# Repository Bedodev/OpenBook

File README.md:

# OpenBook
OpenBook is an open Source eBook Project that aims to create a simple yet powerful esp32-based ebook reader, with quality of life features. 

## Block Diagram

## Simplified BoM
Component | Part # | Source Link
--- | --- | ---
ESP32 | ESP32-C6-WROOM-1-N8 | [Mouser](https://mou.sr/42swLfH)
MicroSD Card Reader | 112A-TAAR-R03 | [DigiKey](https://www.digikey.ro/en/models/17633923)
NOR Flash | W25Q512JVEIQ | [ComponentSearchengine](https://componentsearchengine.com/search?term=W25Q512JVEIQ)
Adafruit Led | SM0603UYC | [SnapEda](https://www.snapeda.com/parts/SM0603UYC/Bivar/view-part/)
Environment Sensor | BME680 | [DigiKey](https://www.digikey.lt/en/models/7401317)
Super Capacitor | CPH3225A-2K | [SnapMagic](https://www.snapeda.com/parts/CPH3225A-2K/Seiko/view-part/)
0402 capsule | RC0402 | [GrabCad](https://grabcad.com/library/tag/0402)
Tantalum Capacitor | TR3B106K025C1300 | [Mouser](https://eu.mouser.com/ProductDetail/Vishay-Sprague/TR3B106K025C1300?qs=jCGqFXxTmLdffnuDkXzk1g%3D%3D)
RTC | DS3231SN# | [ComponentSearchEngine](https://componentsearchengine.com/part-view/DS3231SN%23/Analog%20Devices)
Voltage Detector | BD5229G-TR | [ComponentSearchEngine](https://componentsearchengine.com/part-view/BD5229G-TR/ROHM%20Semiconductor)
Right Angle Switches | EVQ-P7M01P | [Mouser](https://mou.sr/41Z13GK)
Inductor | 784373170680 | [DigiKey](https://www.digikey.ro/en/models/1638502)
Varsistor | CT1812K50G | [ComponentSearchEngine](https://componentsearchengine.com/part-view/CT1812K50G/TDK)
Schottky Diode | SD0805S020S1R0 | [ComponentSearchEngine](https://componentsearchengine.com/part-view/SD0805S020S1R0/Kyocera%20AVX)
Schotty Rectifier | MBR0530 | [ComponentSearchEngine](https://componentsearchengine.com/part-view/MBR0530/onsemi)
ESD Protection | USBLC6-2SC6Y | [ComponentSearchEngine](https://componentsearchengine.com/part-view/USBLC6-2SC6Y/STMicroelectronics)
ESD Suppressors | PGB1010603MR | [ComponentSearchEngine](https://componentsearchengine.com/part-view/PGB1010603MR/LITTELFUSE)
N-MOSFET | Si1308EDL-T1-GE3 | [ComponentSearchEngine](https://componentsearchengine.com/part-view/SI1308EDL-T1-GE3/Vishay)
Qwiic Connector | PRT-14417 | [ComponentSearchEngine](https://componentsearchengine.com/part-view/PRT-14417/SparkFun)
USB Connector | USB4110-GF-A | [ComponentSearchEngine](https://componentsearchengine.com/part-view/USB4110-GF-A/GCT%20(GLOBAL%20CONNECTOR%20TECHNOLOGY))
Display Connector | FH34SRJ-24S-0.5SH(99) | [ComponentSearchEngine](https://componentsearchengine.com/part-view/FH34SRJ-24S-0.5SH(99)/Hirose)
Battery Percentage Chip | MAX17048G+T10 | [ComponentSearchEngine](https://componentsearchengine.com/part-view/MAX17048G%2BT10/Analog%20Devices)
Voltage Reculator | XC6220A331MR-G | [ComponentSearchEngine](https://componentsearchengine.com/part-view/XC6220A331MR-G/Torex)
LiPo Controller | HT7750A | [ComponentSearchengine](https://componentsearchengine.com/part-view/HT7750A%20SOT23-3/Holtek)

## Hardware Overview
  -  **ESP32-C6**: energy efficient RISC based mcu, with wireless connectivity for easy ebook content access and transfer
  -  **eInk Display**: energy efficient black and white display with paper-like look
  -  **Usb-C Port**: easy charging and connectivity with esd protection
  -  **SdCard Reader**: user-accessible expandable storage
  -  **External Flash**: built-in storage for basic functionality
  -  **Real Time Clock**: maintains time data on power off
  -  **Environmental Sensor**: high-accuracy environment data collection for safe usage warnings
  -  **Qwiic Connector**: allows future expandability
  -  **Side Switches**: simple user interfacing with device operations

## ESP32 Pin Mapping
 1. **USB**: user charging and data access
    - IO12 - Usb Data-
    - IO13 - Usb Data+
 2. **GPIO**: user interfacing
    - EN - reset switch, for easy access to chip reset
    - IO9 - "change" switch, for display mode switch
    - IO15 - boot switch, for device startup and shutdown
 2. **SPI**: display, sd card, flash
    - IO2 - MISO, master in slave out, used for data transfer from chip to esp
    - IO7 - MOSI, master out slave in, used for data transfer from esp to chip
    - IO6 - SCK, clock bus sync between esp and chip
    - IO5 - DC, data/command
    - IO3 - busy, for signaling device cannot receive command
 2. **I2C**: battery monitoring, rtc, environment sensing
    - IO21 - SDA, bidirectional serial data line
    - IO22 - SCL, bidirectional serial clock line

## Other comments
 - DRC warnings for the usb allignment pins have to be manually approved
 - Inductor 3D model different from BoM component, but, for development and showcase purposes, footprint and 3D model fit the original

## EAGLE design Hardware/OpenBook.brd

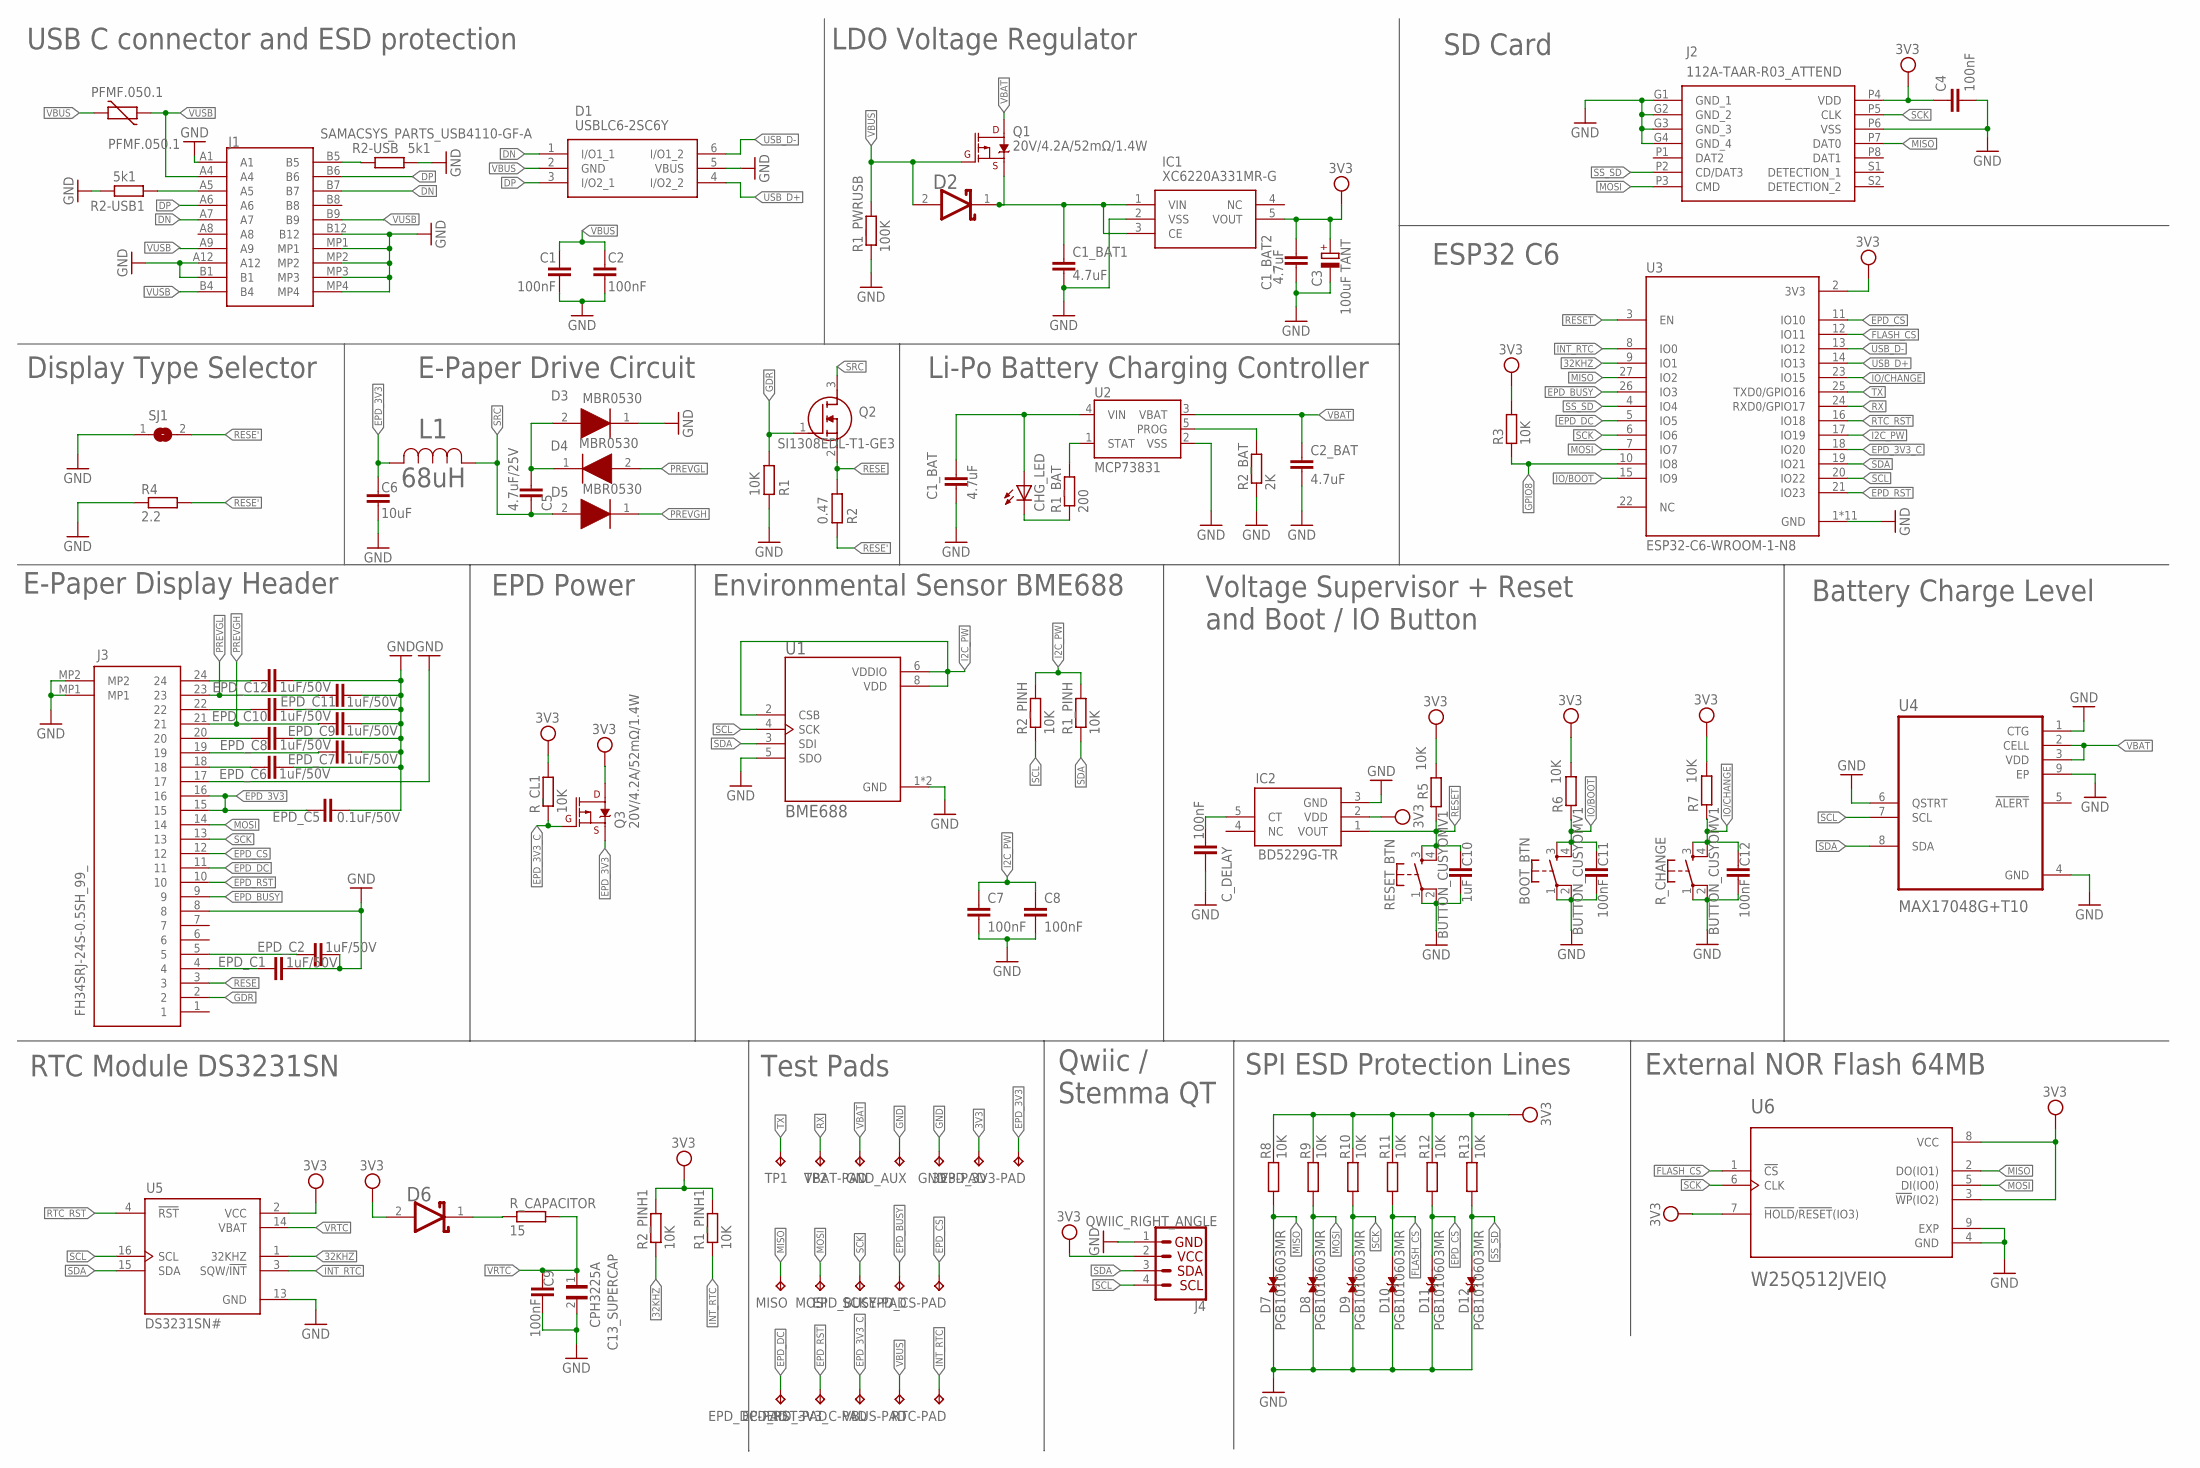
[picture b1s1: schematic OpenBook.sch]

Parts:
3V3-PAD: TPTP20R; TP20R
BOOT_BTN: BUTTON_CUSYOMV1; MYBUTTON
C1, C2: 100nF; ESP32_WROVER_EAGLE-LTSPICE_C0402
C1_BAT, C1_BAT1, C1_BAT2, C2_BAT: 4.7uF; EAGLE-LTSPICE_C0402
C3: 100uF TANT; RCL_CT3528
C4, C7, C8, C9, C11, C12: 100nF; EAGLE-LTSPICE_C0402
C5: 4.7uF/25V; ESP32_WROVER_EAGLE-LTSPICE_C0402
C6: 10uF; ESP32_WROVER_EAGLE-LTSPICE_C0402
C10: 1uF; EAGLE-LTSPICE_C0402
C13_SUPERCAP: CPH3225A; CAPCP3225X100N
CHG_LED: ADAFRUIT_LEDCHIP-LED0603; ADAFRUIT_CHIP-LED0603
C_DELAY: 100nF; EAGLE-LTSPICE_C0402
D1: USBLC6-2SC6Y; SOT95P280X145-6N
D2, D6: ESP32_WROVER_AVX---SD0805S020S1R0_AVX_SD0805S020S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; ESP32_WROVER_AVX---SD0805S020S1R0_AVX_SD0805S020S1R0_0
D3, D4, D5: MBR0530; SOD3716X135N
D7, D8, D9, D10, D11, D12: PGB1010603MR; DIOC1608X36N
EPD_3V3-PAD, EPD_3V3_C-PAD: TPTP20R; TP20R
EPD_BUSY-PAD: TPTP20R; TP20R
EPD_C1, EPD_C2, EPD_C6, EPD_C7, EPD_C8, EPD_C9, EPD_C10, EPD_C11, EPD_C12: 1uF/50V; ESP32_WROVER_EAGLE-LTSPICE_C0402
EPD_C5: 0.1uF/50V; ESP32_WROVER_EAGLE-LTSPICE_C0402
EPD_CS-PAD: TPTP20R; TP20R
EPD_DC-PAD: TPTP20R; TP20R
EPD_RST-PAD: TPTP20R; TP20R
GND: TPTP20R; TP20R
GND_AUX: TPTP20R; TP20R
IC1: XC6220A331MR-G; SOT95P280X120-5N
IC2: BD5229G-TR; SOT95P280X125-5N
J1: SAMACSYS_PARTS_USB4110-GF-A; SAMACSYS_PARTS_USB4110GFA
J2: 112A-TAAR-R03_ATTEND; 112ATAARR03ATTEND
J3: FH34SRJ-24S-0.5SH_99_; FH34SRJ24S05SH99
J4: QWIIC_RIGHT_ANGLE; JST04_1MM_RA
L1: 68uH; IND_4828-WE-TPC_WRE
MISO: TPTP20R; TP20R
MOSI: TPTP20R; TP20R
PFMF.050.1: PFMF.050.1; ESP32C6_VARISTOR_CT/CN1812
Q1, Q3: 20V/4.2A/52mΩ/1.4W; ESP32_WROVER_SPARKFUN-DISCRETESEMI_SOT23-3
Q2: SI1308EDL-T1-GE3; SOT65P210X110-3N
R1, R1_PINH, R1_PINH1, R2_PINH, R2_PINH1, R3, R5, R6, R7, R8, R9, R10, R11, R12, R13: 10K; ESP32_WROVER_EAGLE-LTSPICE_R0402
R1_BAT: 200; ESP32_WROVER_EAGLE-LTSPICE_R0402
R1_PWRUSB: 100K; ESP32_WROVER_EAGLE-LTSPICE_R0402
R2: 0.47; ESP32_WROVER_EAGLE-LTSPICE_R0402
R2-USB, R2-USB1: 5k1; ESP32_WROVER_EAGLE-LTSPICE_R0402
R2_BAT: 2K; ESP32_WROVER_EAGLE-LTSPICE_R0402
R4: 2.2; ESP32_WROVER_EAGLE-LTSPICE_R0402
RESET_BTN: BUTTON_CUSYOMV1; MYBUTTON
RTC-PAD: TPTP20R; TP20R
R_CAPACITOR: 15; ESP32_WROVER_EAGLE-LTSPICE_R0402
R_CHANGE: BUTTON_CUSYOMV1; MYBUTTON
R_CL1: 10K; ESP32_WROVER_EAGLE-LTSPICE_R0402
SCK: TPTP20R; TP20R
SJ1: SJ
TP1, TP2: TPTP20R; TP20R
U1: BME688; ESP32_WROVER_BME680_PSON80P300X300X100-8N
U2: MCP73831; ESP32_WROVER_SPARKFUN-IC-POWER_SOT23-5
U3: ESP32-C6-WROOM-1-N8; XCVR_ESP32-C6-WROOM-1-N8
U4: MAX17048G+T10; SON50P200X200X80-9N
U5: DS3231SN#; SOIC127P1032X265-16N
U6: W25Q512JVEIQ; SON127P600X800X80-9N
VBAT-PAD: TPTP20R; TP20R
VBUS-PAD: TPTP20R; TP20R

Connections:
3V3: 3V3-PAD.TP, C1_BAT2.1, C3.+, C4.1, D6.2 (ANODE), IC1.5 (VOUT), IC2.2 (VDD), J2.P4 (VDD), J4.2, Q3.3 (D), R1_PINH1.2, R2_PINH1.2, R3.2, R5.2, R6.2, R7.2, R8.2, R9.2, R10.2, R11.2, R12.2, R13.2, R_CL1.2, U3.2 (3V3), U5.2 (VCC), U6.3 (!WP!(IO2)), U6.7 (!HOLD!/!RESET!(IO3)), U6.8 (VCC)
32KHZ: R2_PINH1.1, U3.9 (IO1), U5.1 (32KHZ)
DN: D1.1 (I/O1_1), J1.A7, J1.B7
DP: D1.3 (I/O2_1), J1.A6, J1.B6
EPD_3V3: C6.1, EPD_3V3-PAD.TP, EPD_C5.1, J3.15, J3.16, L1.2, Q3.2 (S)
EPD_3V3_C: EPD_3V3_C-PAD.TP, Q3.1 (G), R_CL1.1, U3.18 (IO20)
EPD_BUSY: EPD_BUSY-PAD.TP, J3.9, U3.26 (IO3)
EPD_CS: D11.2, EPD_CS-PAD.TP, J3.12, R12.1, U3.11 (IO10)
EPD_DC: EPD_DC-PAD.TP, J3.11, U3.5 (IO5)
EPD_RST: EPD_RST-PAD.TP, J3.10, U3.21 (IO23)
FLASH_CS: D10.2, R11.1, U3.12 (IO11), U6.1 (!CS)
GDR: J3.2, Q2.1 (G), R1.2
GND: BOOT_BTN.1, BOOT_BTN.2, C1.2, C1_BAT.2, C1_BAT1.2, C1_BAT2.2, C2.2, C2_BAT.2, C3.-, C4.2, C6.2, C7.2, C8.2, C9.2, C10.2, C11.2, C12.2, C13_SUPERCAP.2, C_DELAY.2, D1.5 (VBUS), D3.1 (K), D7.1, D8.1, D9.1, D10.1, D11.1, D12.1, EPD_C1.1, EPD_C2.1, EPD_C5.2, EPD_C6.2, EPD_C7.2, EPD_C8.2, EPD_C9.2, EPD_C10.2, EPD_C11.2, EPD_C12.2, GND.TP, GND_AUX.TP, IC1.2 (VSS), IC2.3 (GND), J1.A1, J1.A12, J1.B1, J1.B12, J1.MP1, J1.MP2, J1.MP3, J1.MP4, J2.G1 (GND_1), J2.G2 (GND_2), J2.G3 (GND_3), J2.G4 (GND_4), J2.P6 (VSS), J3.8, J3.17, J3.MP1, J3.MP2, J4.1, R1.1, R1_PWRUSB.1, R2-USB.2, R2-USB1.1, R2_BAT.1, R4.1, RESET_BTN.1, RESET_BTN.2, R_CHANGE.1, R_CHANGE.2, SJ1.1, U1.1 (GND), U1.5 (SDO), U1.7 (GND), U2.2 (VSS), U3.1 (GND), U3.28 (GND), U3.29_1 (GND), U3.29_2 (GND), U3.29_3 (GND), U3.29_4 (GND), U3.29_5 (GND), U3.29_6 (GND), U3.29_7 (GND), U3.29_8 (GND), U3.29_9 (GND), U4.1 (CTG), U4.4 (GND), U4.6 (QSTRT), U4.9 (EP), U5.13 (GND), U6.4 (GND), U6.9 (EXP)
GPIO8: R3.1, U3.10 (IO8)
I2C_PW: C7.1, C8.1, R1_PINH.2, R2_PINH.2, U1.2 (CSB), U1.6 (VDDIO), U1.8 (VDD), U3.17 (IO19)
INT_RTC: R1_PINH1.1, RTC-PAD.TP, U3.8 (IO0), U5.3 (SQW/!INT)
IO/BOOT: BOOT_BTN.3, BOOT_BTN.4, C11.1, R6.1, U3.15 (IO9)
IO/CHANGE: C12.1, R7.1, R_CHANGE.3, R_CHANGE.4, U3.23 (IO15)
MISO: D7.2, J2.P7 (DAT0), MISO.TP, R8.1, U3.27 (IO2), U6.2 (DO(IO1))
MOSI: D8.2, J2.P3 (CMD), J3.14, MOSI.TP, R9.1, U3.7 (IO7), U6.5 (DI(IO0))
unnamed: J1.A5, R2-USB1.2
unnamed: J1.B5, R2-USB.1
unnamed: C1_BAT1.1, D2.1 (CATHODE), IC1.1 (VIN), IC1.3 (CE), Q1.2 (S)
unnamed: C5.1, D3.2 (A), D4.1 (K)
unnamed: EPD_C1.2, J3.4
unnamed: EPD_C2.2, J3.5
unnamed: EPD_C6.1, J3.18
unnamed: EPD_C7.1, J3.19
unnamed: EPD_C8.1, J3.20
unnamed: R2_BAT.2, U2.5 (PROG)
unnamed: EPD_C10.1, J3.22
unnamed: R1_BAT.2, U2.1 (STAT)
unnamed: EPD_C12.1, J3.24
unnamed: CHG_LED.C, R1_BAT.1
unnamed: C1_BAT.1, CHG_LED.A, U2.4 (VIN)
unnamed: C_DELAY.1, IC2.5 (CT)
unnamed: D6.1 (CATHODE), R_CAPACITOR.1
PREVGH: D5.1 (K), EPD_C9.1, J3.21
PREVGL: D4.2 (A), EPD_C11.1, J3.23
RESE: J3.3, Q2.2 (S), R2.2
RESE': R2.1, R4.2, SJ1.2
RESET: C10.1, IC2.1 (VOUT), R5.1, RESET_BTN.3, RESET_BTN.4, U3.3 (EN)
RTC_RST: U3.16 (IO18), U5.4 (!RST)
RX: TP2.TP, U3.24 (RXD0/GPIO17)
SCK: D9.2, J2.P5 (CLK), J3.13, R10.1, SCK.TP, U3.6 (IO6), U6.6 (CLK)
SCL: J4.4, R2_PINH.1, U1.4 (SCK), U3.20 (IO22), U4.7 (SCL), U5.16 (SCL)
SDA: J4.3, R1_PINH.1, U1.3 (SDI), U3.19 (IO21), U4.8 (SDA), U5.15 (SDA)
SRC: C5.2, D5.2 (A), L1.1, Q2.3 (D)
SS_SD: D12.2, J2.P2 (CD/DAT3), R13.1, U3.4 (IO4)
TX: TP1.TP, U3.25 (TXD0/GPIO16)
USB_D+: D1.4 (I/O2_2), U3.14 (IO13)
USB_D-: D1.6 (I/O1_2), U3.13 (IO12)
VBAT: C2_BAT.1, Q1.3 (D), U2.3 (VBAT), U4.2 (CELL), U4.3 (VDD), VBAT-PAD.TP
VBUS: C1.1, C2.1, D1.2 (GND), D2.2 (ANODE), PFMF.050.1.2, Q1.1 (G), R1_PWRUSB.2, VBUS-PAD.TP
VRTC: C9.1, C13_SUPERCAP.1, R_CAPACITOR.2, U5.14 (VBAT)
VUSB: J1.A4, J1.A9, J1.B4, J1.B9, PFMF.050.1.1

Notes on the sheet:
USB C connector and ESD protection
Display Type Selector
E-Paper Drive Circuit
E-Paper Display Header
EPD Power
LDO Voltage Regulator
Li-Po Battery Charging Controller
SD Card
ESP32 C6
Battery Charge Level
Environmental Sensor BME688
Voltage Supervisor + Reset and Boot / IO Button
RTC Module DS3231SN
Test Pads
Qwiic / Stemma QT
SPI ESD Protection Lines
External NOR Flash 64MB

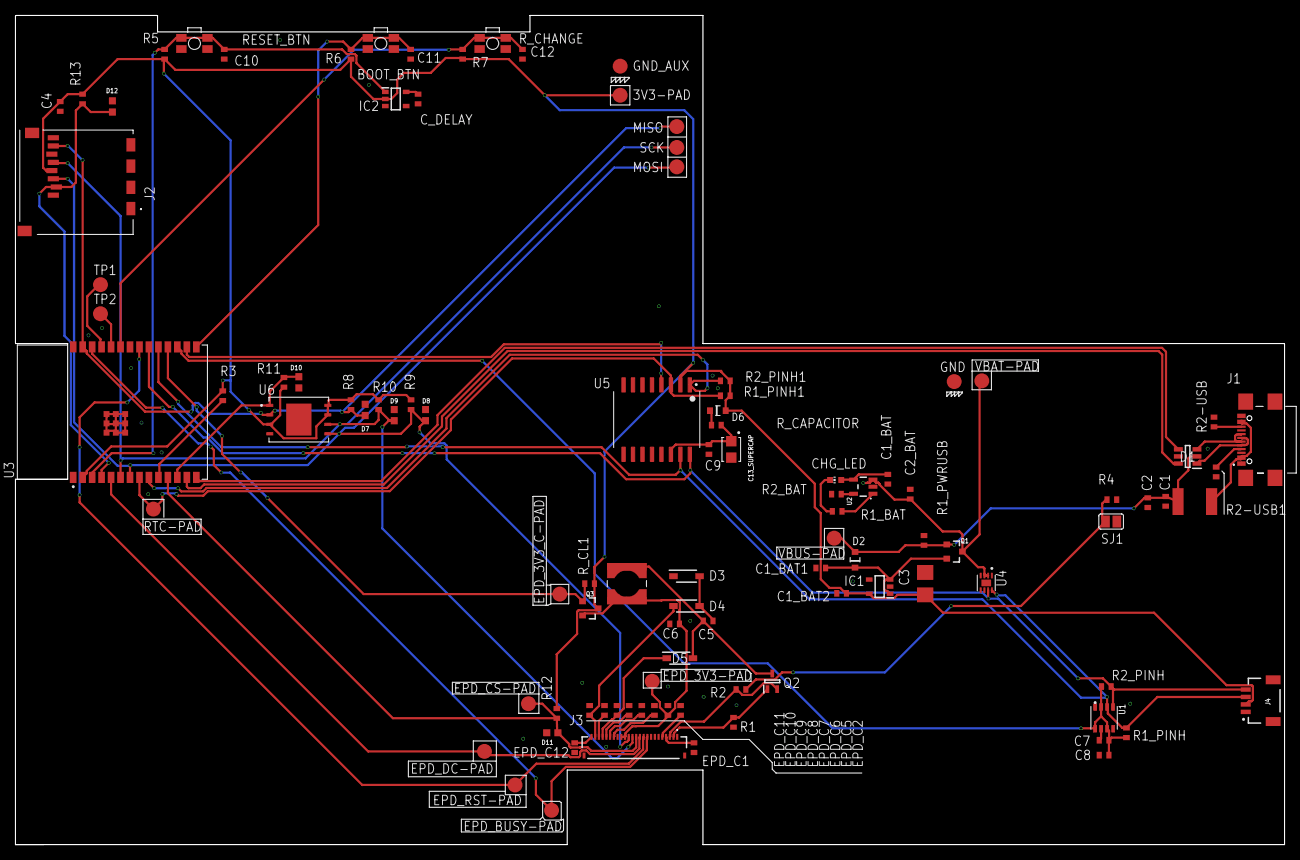
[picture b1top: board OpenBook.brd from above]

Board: 2 copper layers, 170.2 x 111.2 mm, 103 parts (0 on the bottom side), 56 nets.

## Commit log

2025-04-06 Added Diagram link to README
2025-04-06 Inital Commit
2025-04-14 Fixed some stuff
    +Added via stitching around mcu
    +Fixed inductor footprint with pads
    +Added missing values to resistors
    +Approved redundent erc warnings
    +Fixed unconnected nets
2025-04-14 Updated Screen Fitment
    Updated Pcb Size from the default 1.6mm to the required 1mm for screen to fit properly

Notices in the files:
parts and their libraries:
COPYRIGHT: Copyright (C) 2024 Ultra Librarian. All rights reserved.
